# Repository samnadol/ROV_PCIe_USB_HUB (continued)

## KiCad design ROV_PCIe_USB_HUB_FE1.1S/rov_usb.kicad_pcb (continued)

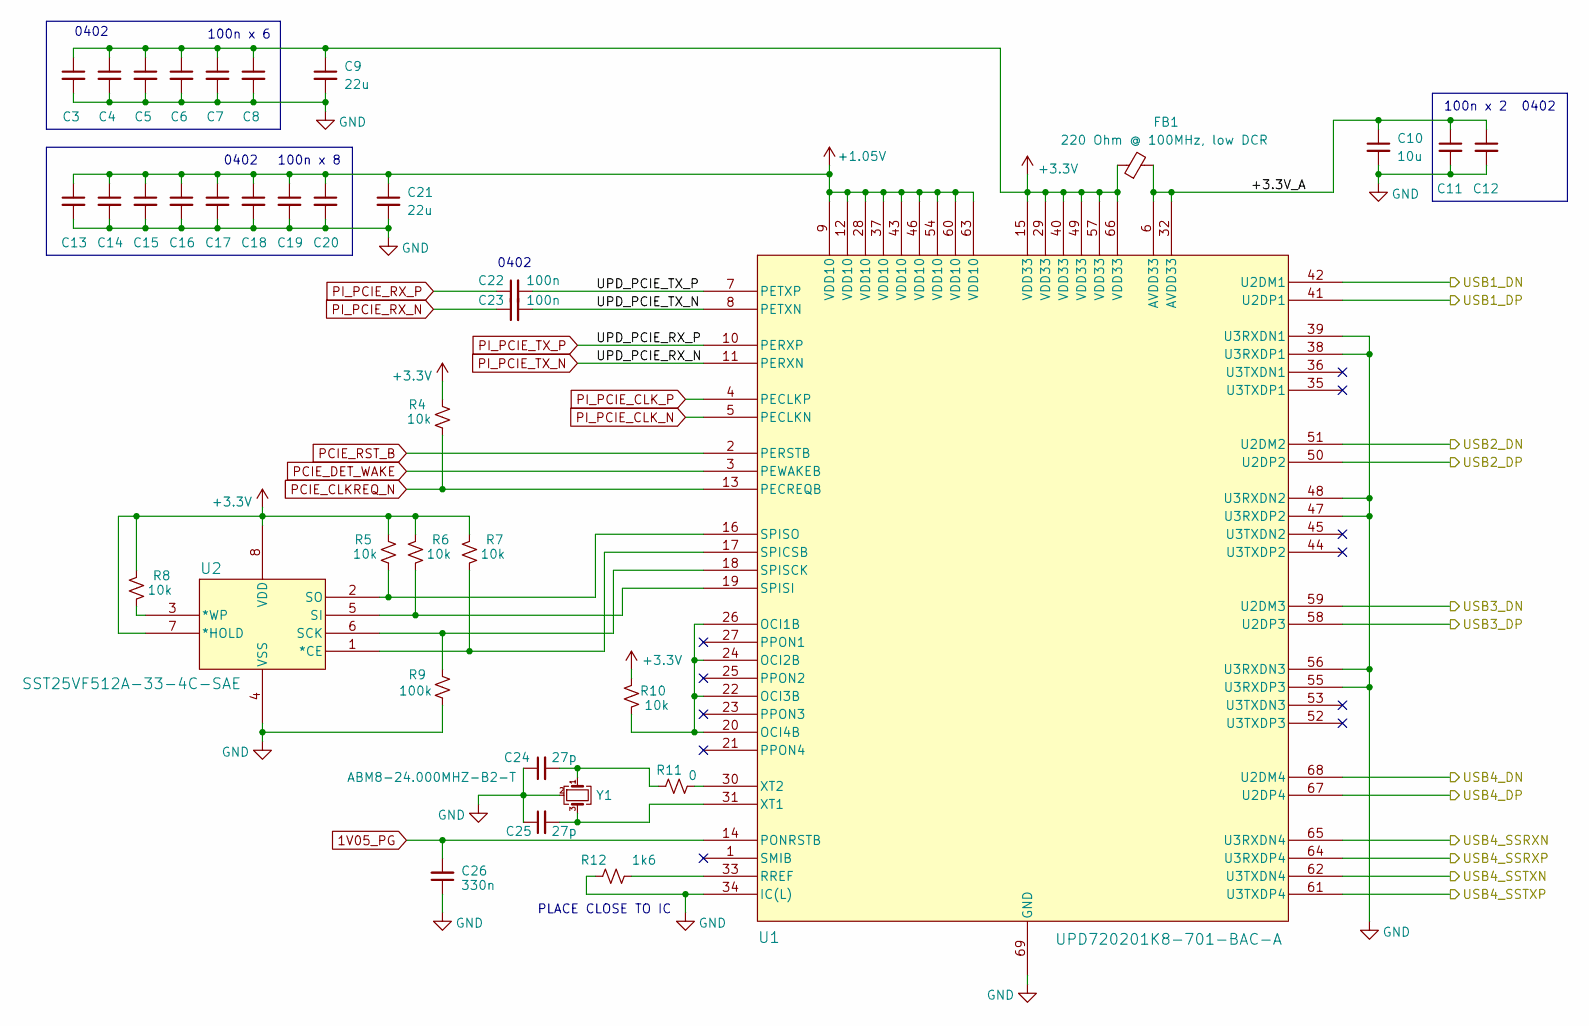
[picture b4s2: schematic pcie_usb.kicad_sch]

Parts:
C3, C4, C5, C6, C7, C8, C11, C12, C13, C14, C15, C16, C17, C18, C19, C20, C22, C23: 100n; C_0402_1005Metric; Part Number CL05B104KO5NNNC
C9, C21: 22u; C_0805_2012Metric; Part Number CL21A226MOQNNNE
C10: 10u; C_0805_2012Metric; Part Number CL21A106KOQNNNE
C24, C25: 27p; C_0402_1005Metric; Part Number CL05C270JB5NNNC
C26: 330n; C_0402_1005Metric; Part Number CL05A334KQ5NNNC
FB1: 220 Ohm @ 100MHz, low DCR; L_0805_2012Metric; Part Number BLM21PG221SN1D
R4, R5, R6, R7, R8, R10: 10k; R_0603_1608Metric; Part Number RC0603FR-0710KL
R9: 100k; R_0603_1608Metric; Part Number RC0603FR-07100KL
R11: 0; R_0402_1005Metric; Part Number RC0402JR-070RL
R12: 1k6; R_0603_1608Metric; Part Number RC0603FR-071K6L
U1: UPD720201K8-701-BAC-A; QFN68_8X8_REN; Part Number UPD720201K8-701-BAC-A
U2: SST25VF512A-33-4C-SAE; SST25VF512A; Part Number SST25VF512A-33-4C-SAE
Y1: ABM8-24.000MHZ-B2-T; Crystal_SMD_3225-4Pin_3.2x2.5mm; Part Number ABM8-24.000MHZ-B2-T

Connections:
1V05_PG: C26.2, U1.14 (PONRSTB); also elsewhere on the board
+1.05V: C13.1, C14.1, C15.1, C16.1, C17.1, C18.1, C19.1, C20.1, C21.1, U1.9 (VDD10), U1.12 (VDD10), U1.28 (VDD10), U1.37 (VDD10), U1.43 (VDD10), U1.46 (VDD10), U1.54 (VDD10), U1.60 (VDD10), U1.63 (VDD10); also elsewhere on the board
+3.3V: C3.1, C4.1, C5.1, C6.1, C7.1, C8.1, C9.1, FB1.1, R4.1, R5.1, R6.1, R7.1, R8.1, R10.1, U1.15 (VDD33), U1.29 (VDD33), U1.40 (VDD33), U1.49 (VDD33), U1.57 (VDD33), U1.66 (VDD33), U2.7 (*HOLD), U2.8 (VDD); also elsewhere on the board
/PCIe_USB/+3.3V_A: C10.1, C11.1, C12.1, FB1.2, U1.6 (AVDD33), U1.32 (AVDD33)
/PCIe_USB/UPD_PCIE_TX_N: C23.2, U1.8 (PETXN)
/PCIe_USB/UPD_PCIE_TX_P: C22.2, U1.7 (PETXP)
/PCIe_USB/USB1_DN: U1.42 (U2DM1); also elsewhere on the board
/PCIe_USB/USB1_DP: U1.41 (U2DP1); also elsewhere on the board
/PCIe_USB/USB2_DN: U1.51 (U2DM2); also elsewhere on the board
/PCIe_USB/USB2_DP: U1.50 (U2DP2); also elsewhere on the board
/PCIe_USB/USB3_DN: U1.59 (U2DM3); also elsewhere on the board
/PCIe_USB/USB3_DP: U1.58 (U2DP3); also elsewhere on the board
/PCIe_USB/USB4_DN: U1.68 (U2DM4); also elsewhere on the board
/PCIe_USB/USB4_DP: U1.67 (U2DP4); also elsewhere on the board
/PCIe_USB/USB4_SSRXN: U1.65 (U3RXDN4); also elsewhere on the board
/PCIe_USB/USB4_SSRXP: U1.64 (U3RXDP4); also elsewhere on the board
/PCIe_USB/USB4_SSTXN: U1.62 (U3TXDN4); also elsewhere on the board
/PCIe_USB/USB4_SSTXP: U1.61 (U3TXDP4); also elsewhere on the board
GND: C3.2, C4.2, C5.2, C6.2, C7.2, C8.2, C9.2, C10.2, C11.2, C12.2, C13.2, C14.2, C15.2, C16.2, C17.2, C18.2, C19.2, C20.2, C21.2, C24.1, C25.1, C26.1, R9.2, R12.1, U1.34 (IC(L)), U1.38 (U3RXDP1), U1.39 (U3RXDN1), U1.47 (U3RXDP2), U1.48 (U3RXDN2), U1.55 (U3RXDP3), U1.56 (U3RXDN3), U1.69 (GND), U2.4 (VSS), Y1.2 (G), Y1.4 (G); also elsewhere on the board
unnamed: C24.2, R11.1, Y1.1
unnamed: R10.2, U1.20 (OCI4B), U1.22 (OCI3B), U1.24 (OCI2B), U1.26 (OCI1B)
unnamed: R12.2, U1.33 (RREF)
unnamed: R7.2, U1.17 (SPICSB), U2.1 (*CE)
unnamed: R9.1, U1.18 (SPISCK), U2.6 (SCK)
unnamed: R6.2, U1.19 (SPISI), U2.5 (SI)
unnamed: R5.2, U1.16 (SPISO), U2.2 (SO)
unnamed: C25.2, U1.31 (XT1), Y1.3
unnamed: R11.2, U1.30 (XT2)
unnamed: R8.2, U2.3 (*WP)
PCIE_CLKREQ_N: R4.2, U1.13 (PECREQB); also elsewhere on the board
PCIE_DET_WAKE: U1.3 (PEWAKEB); also elsewhere on the board
PCIE_RST_B: U1.2 (PERSTB); also elsewhere on the board
PI_PCIE_CLK_N: U1.5 (PECLKN); also elsewhere on the board
PI_PCIE_CLK_P: U1.4 (PECLKP); also elsewhere on the board
PI_PCIE_RX_N: C23.1; also elsewhere on the board
PI_PCIE_RX_P: C22.1; also elsewhere on the board
PI_PCIE_TX_N: U1.11 (PERXN); also elsewhere on the board
PI_PCIE_TX_P: U1.10 (PERXP); also elsewhere on the board

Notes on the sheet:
0402
100n x 6
100n x 2
PLACE CLOSE TO IC
100n x 8

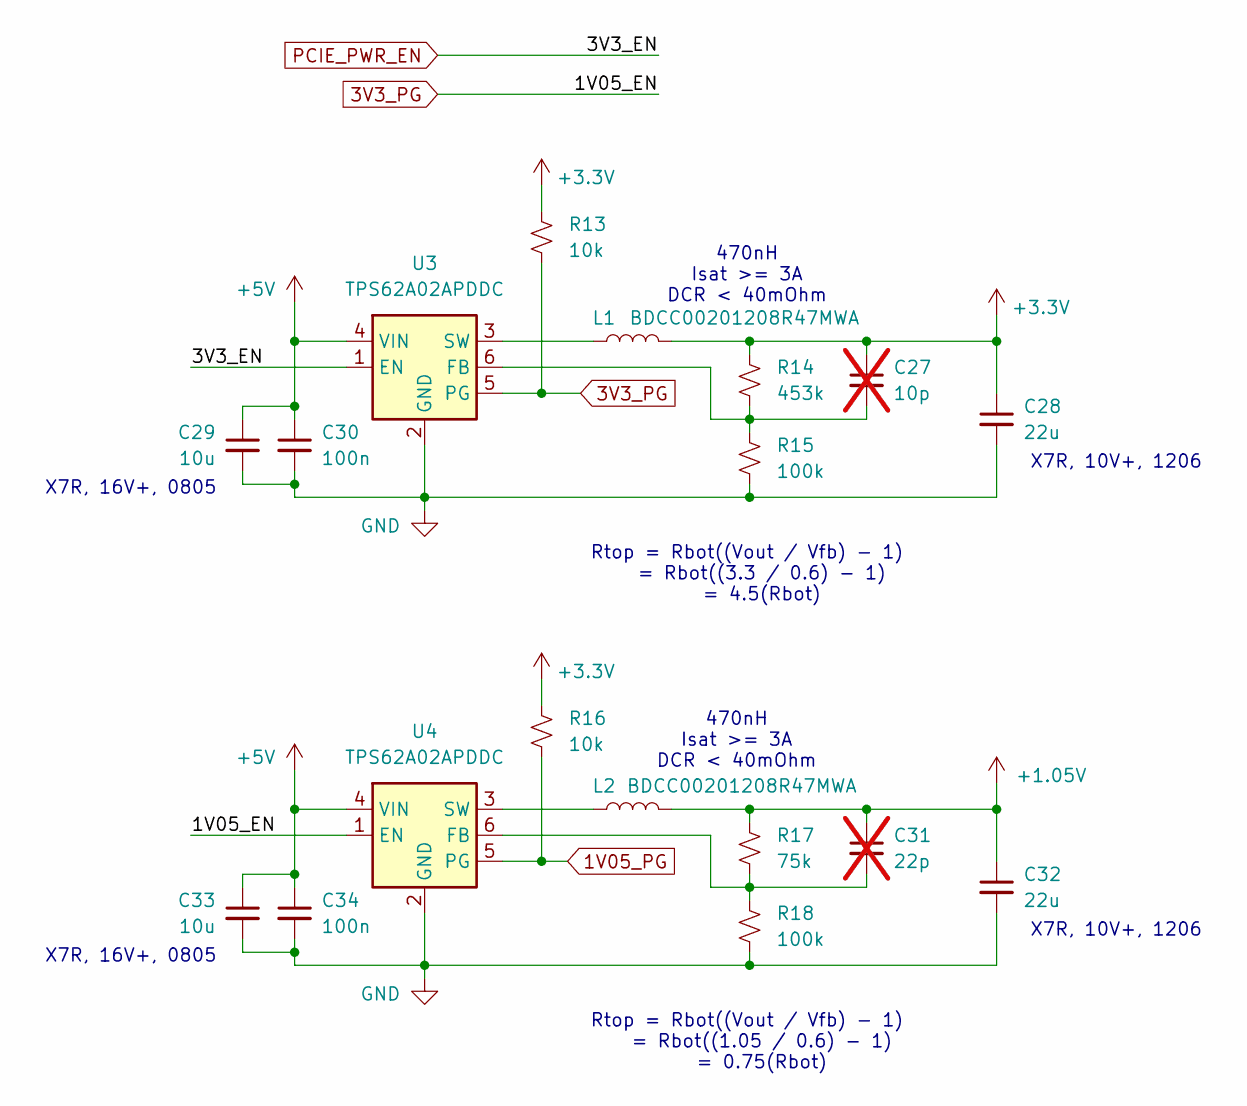
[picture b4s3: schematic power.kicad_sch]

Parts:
C27: 10p; C_0402_1005Metric; Part Number CL05C100JB5NNNC; not fitted
C28, C32: 22u; C_0805_2012Metric; Part Number CL21A226MOQNNNE
C29, C33: 10u; C_0805_2012Metric; Part Number CL21A106KOQNNNE
C30, C34: 100n; C_0402_1005Metric; Part Number CL05B104KO5NNNC
C31: 22p; C_0402_1005Metric; Part Number CL05C180JB5NNNC; not fitted
L1, L2: BDCC00201208R47MWA; L_0805_2012Metric; Part Number BDCC00201208R47MWA
R13, R16: 10k; R_0603_1608Metric; Part Number RC0603FR-0710KL
R14: 453k; R_0603_1608Metric; Part Number RC0603FR-07453KL
R15, R18: 100k; R_0603_1608Metric; Part Number RC0603FR-07100KL
R17: 75k; R_0603_1608Metric; Part Number RC0603FR-0775KL
U3, U4: TPS62A02APDDC; SOT-23-6; Part Number TPS62A02APDDC

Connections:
1V05_PG: R16.2, U4.5 (PG); also elsewhere on the board
3V3_PG: R13.2, U3.5 (PG), U4.1 (EN)
+1.05V: C31.1, C32.1, L2.2, R17.1; also elsewhere on the board
+3.3V: C27.1, C28.1, L1.2, R13.1, R14.1, R16.1; also elsewhere on the board
+5V: C29.1, C30.1, C33.1, C34.1, U3.4 (VIN), U4.4 (VIN); also elsewhere on the board
GND: C28.2, C29.2, C30.2, C32.2, C33.2, C34.2, R15.2, R18.2, U3.2 (GND), U4.2 (GND); also elsewhere on the board
unnamed: C27.2, R14.2, R15.1, U3.6 (FB)
unnamed: L1.1, U3.3 (SW)
unnamed: C31.2, R17.2, R18.1, U4.6 (FB)
unnamed: L2.1, U4.3 (SW)
PCIE_PWR_EN: U3.1 (EN); also elsewhere on the board

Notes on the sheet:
X7R, 10V+, 1206
470nH Isat >= 3A DCR < 40mOhm
X7R, 16V+, 0805
Rtop = Rbot((Vout / Vfb) - 1) = Rbot((3.3 / 0.6) - 1) = 4.5(Rbot)
Rtop = Rbot((Vout / Vfb) - 1) = Rbot((1.05 / 0.6) - 1) = 0.75(Rbot)

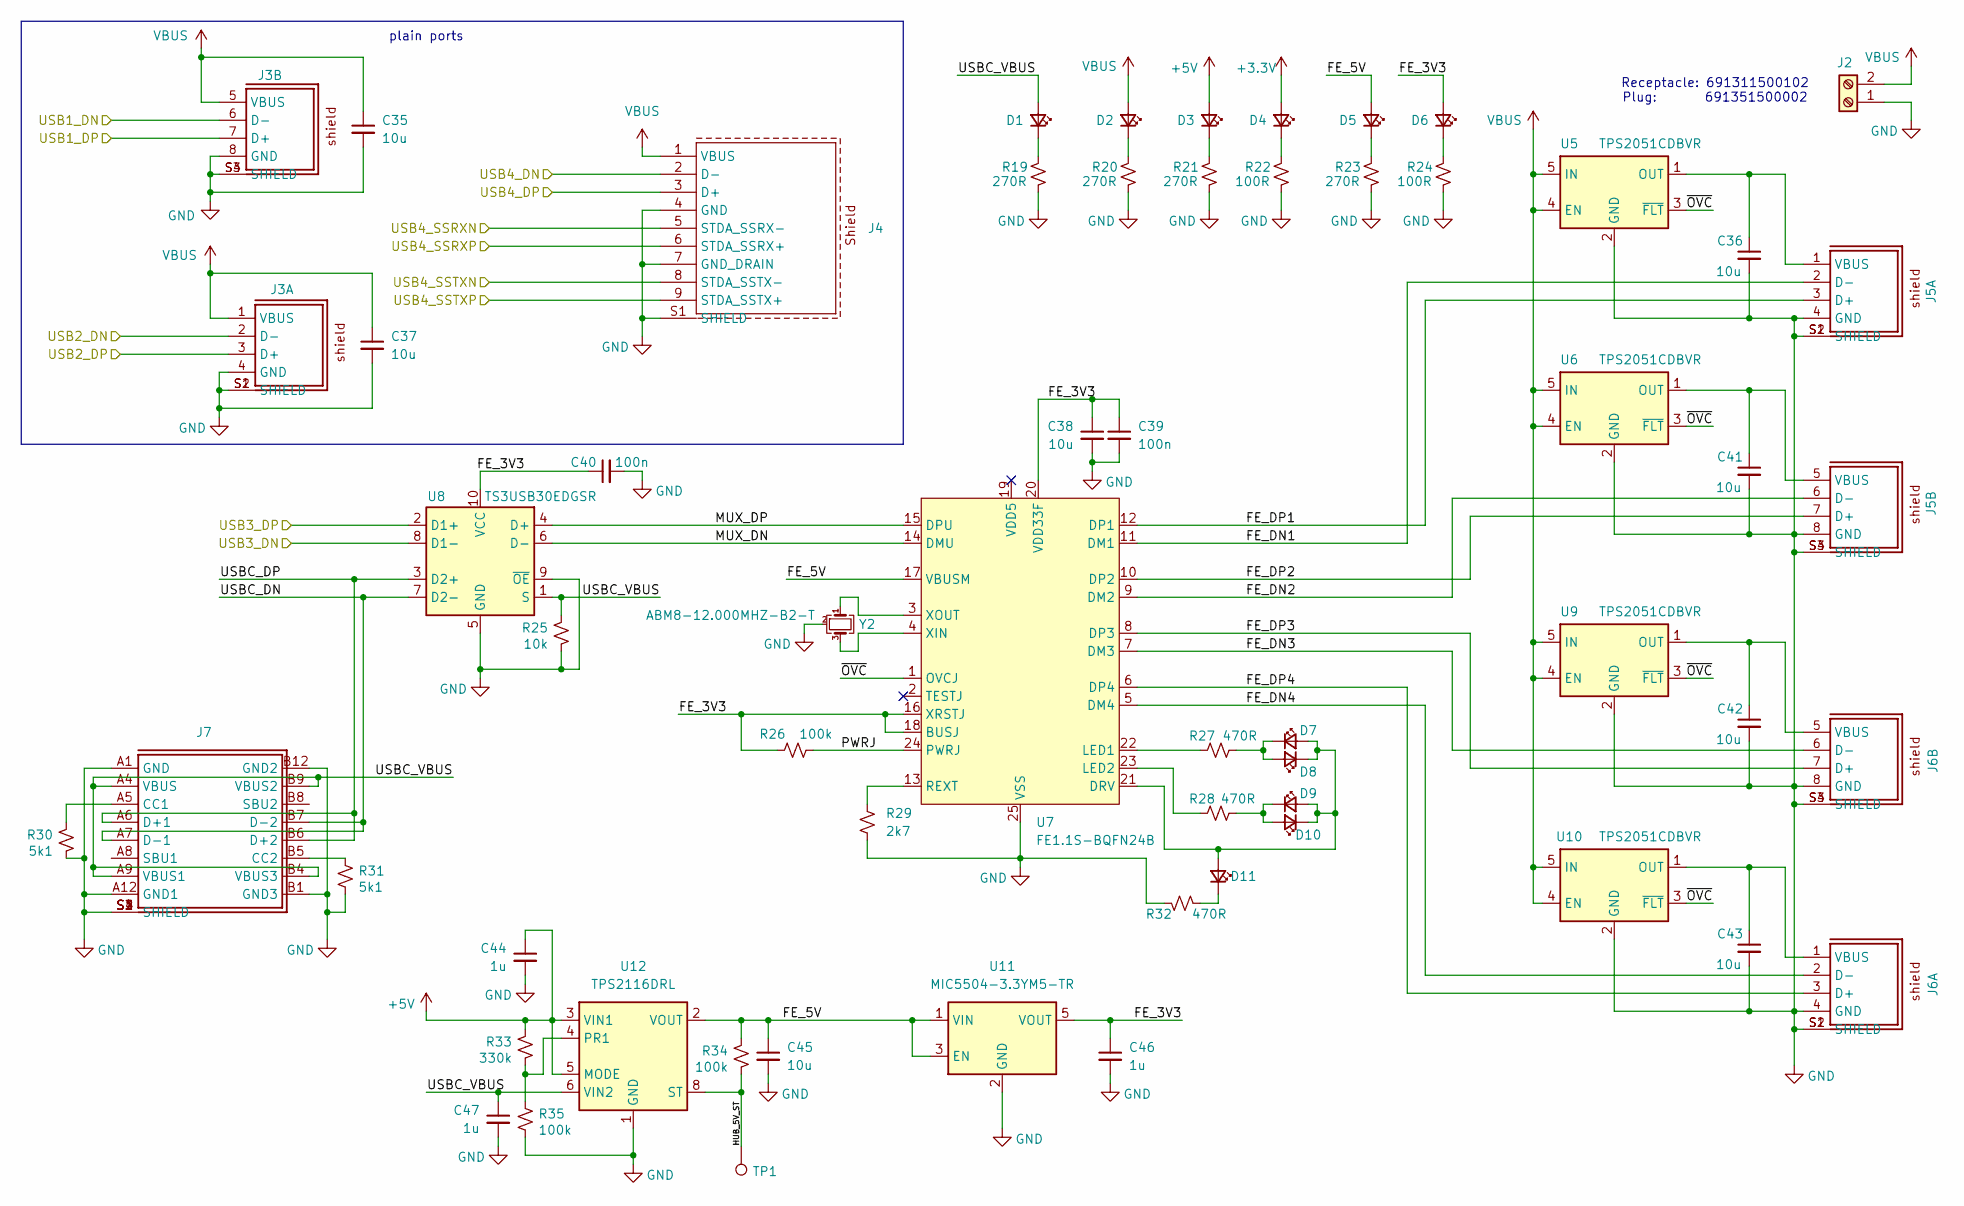
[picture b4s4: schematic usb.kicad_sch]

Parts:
C35, C36, C37, C38, C41, C42, C43, C45: 10u; C_0805_2012Metric; Part Number CL21A106KOQNNNE
C39, C40: 100n; C_0402_1005Metric; Part Number CL05B104KO5NNNC
C44, C46, C47: 1u; C_0603_1608Metric; Part Number CL10B105KO8NNNC
D1, D2, D3, D4, D5, D6, D7, D8, D9, D10: Green; LED_0603_1608Metric; Part Number LTST-C190KGKT
D11: Red; LED_0603_1608Metric; Part Number LTST-C191KRKT
J2: 691311500102; J_Wurth_WR-TBL_691311500102; Part Number 691311500102
J3, J5, J6: USB-A-D-RA; J_Wurth_WR-USB_61400826021; Working Voltage (V (AC)) 30; Part Number USB-A-D-RA
J4: USB-A3-S-VT-CS5A; J_Wurth_WR-USB_692121430000; Working Voltage(V (AC)) 30 V (AC); Part Number USB-A3-S-VT-CS5A
J7: 629722000214; J_Wurth_WR-USB_629722000214; Working Voltage (V (AC)) 20; Part Number 629722000214
R19, R20, R21, R23: 270R; R_0603_1608Metric; Part Number RC0603FR-07270RL
R22, R24: 100R; R_0603_1608Metric; Part Number RC0603FR-07100RL
R25: 10k; R_0603_1608Metric; Part Number RC0603FR-0710KL
R26, R34, R35: 100k; R_0603_1608Metric; Part Number RC0603FR-07100KL
R27, R28, R32: 470R; R_0603_1608Metric; Part Number RC0603FR-07470RL
R29: 2k7; R_0603_1608Metric; Part Number RC0603FR-072K7L
R30, R31: 5k1; R_0603_1608Metric; Part Number RC0603FR-075K1L
R33: 330k; R_0603_1608Metric; Part Number RC0603FR-07330KL
TP1: TestPoint; TestPoint_Pad_1.0x1.0mm
U5, U6, U9, U10: TPS2051CDBVR; SOT-23-5; Part Number TPS2051CDBVR
U7: FE1.1S-BQFN24B; WQFN-24-1EP_4x4mm_P0.5mm_EP2.45x2.45mm; Part Number FE1.1S-BQFN24B
U8: TS3USB30EDGSR; TSSOP-10_3x3mm_P0.5mm; Part Number TS3USB30EDGSR
U11: MIC5504-3.3YM5-TR; SOT-23-5; Part Number MIC5504-3.3YM5-TR
U12: TPS2116DRL; SOT-583-8; Part Number TPS2116DRL
Y2: ABM8-12.000MHZ-B2-T; Crystal_SMD_3225-4Pin_3.2x2.5mm; Part Number ABM8-12.000MHZ-B2-T

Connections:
+3.3V: D4.2 (A); also elsewhere on the board
+5V: C44.1, D3.2 (A), R33.2, U12.3 (VIN1), U12.5 (MODE); also elsewhere on the board
/PCIe_USB/USB1_DN: J3.6 (D-); also elsewhere on the board
/PCIe_USB/USB1_DP: J3.7 (D+); also elsewhere on the board
/PCIe_USB/USB2_DN: J3.2 (D-); also elsewhere on the board
/PCIe_USB/USB2_DP: J3.3 (D+); also elsewhere on the board
/PCIe_USB/USB3_DN: U8.8 (D1-); also elsewhere on the board
/PCIe_USB/USB3_DP: U8.2 (D1+); also elsewhere on the board
/PCIe_USB/USB4_DN: J4.2 (D-); also elsewhere on the board
/PCIe_USB/USB4_DP: J4.3 (D+); also elsewhere on the board
/PCIe_USB/USB4_SSRXN: J4.5 (STDA_SSRX-); also elsewhere on the board
/PCIe_USB/USB4_SSRXP: J4.6 (STDA_SSRX+); also elsewhere on the board
/USB/FE_3V3: C38.1, C39.1, C40.1, C46.1, D6.2 (A), R26.2, U7.16 (XRSTJ), U7.18 (BUSJ), U7.20 (VDD33F), U8.10 (VCC), U11.5 (VOUT)
/USB/FE_5V: C45.1, D5.2 (A), R34.2, U7.17 (VBUSM), U11.1 (VIN), U11.3 (EN), U12.2 (VOUT), U12.7 (VOUT)
/USB/FE_DN1: J5.2 (D-), U7.11 (DM1)
/USB/FE_DN2: J5.6 (D-), U7.9 (DM2)
/USB/FE_DN3: J6.6 (D-), U7.7 (DM3)
/USB/FE_DN4: J6.2 (D-), U7.5 (DM4)
/USB/FE_DP1: J5.3 (D+), U7.12 (DP1)
/USB/FE_DP2: J5.7 (D+), U7.10 (DP2)
/USB/FE_DP3: J6.7 (D+), U7.8 (DP3)
/USB/FE_DP4: J6.3 (D+), U7.6 (DP4)
/USB/HUB_5V_ST: R34.1, TP1.1 (1_1), U12.8 (ST)
/USB/MUX_DN: U7.14 (DMU), U8.6 (D-)
/USB/MUX_DP: U7.15 (DPU), U8.4 (D+)
/USB/PWRJ: R26.1, U7.24 (PWRJ)
/USB/USB4_SSTXN: J4.8 (STDA_SSTX-); also elsewhere on the board
/USB/USB4_SSTXP: J4.9 (STDA_SSTX+); also elsewhere on the board
/USB/USBC_DN: J7.A7 (D-1), J7.B7 (D-2), U8.7 (D2-)
/USB/USBC_DP: J7.A6 (D+1), J7.B6 (D+2), U8.3 (D2+)
/USB/USBC_VBUS: C47.1, D1.2 (A), J7.A4 (VBUS), J7.A9 (VBUS1), J7.B4 (VBUS3), J7.B9 (VBUS2), R25.2, U8.1 (S), U12.6 (VIN2)
/USB/~OVC: U5.3 (~FLT), U6.3 (~FLT), U7.1 (OVCJ), U9.3 (~FLT), U10.3 (~FLT)
GND: C35.2, C36.2, C37.2, C38.2, C39.2, C40.2, C41.2, C42.2, C43.2, C44.2, C45.2, C46.2, C47.2, J2.1, J3.4 (GND), J3.8 (GND), J3.S1 (SHIELD), J3.S2 (SHIELD), J3.S3 (SHIELD), J3.S4 (SHIELD), J4.4 (GND), J4.7 (GND_DRAIN), J4.S1 (SHIELD), J4.S2 (SHIELD), J5.4 (GND), J5.8 (GND), J5.S1 (SHIELD), J5.S2 (SHIELD), J5.S3 (SHIELD), J5.S4 (SHIELD), J6.4 (GND), J6.8 (GND), J6.S1 (SHIELD), J6.S2 (SHIELD), J6.S3 (SHIELD), J6.S4 (SHIELD), J7.A1 (GND), J7.A12 (GND1), J7.B1 (GND3), J7.B12 (GND2), J7.S1 (SHIELD), J7.S2 (SHIELD), J7.S3 (SHIELD), J7.S4 (SHIELD), R19.1, R20.1, R21.1, R22.1, R23.1, R24.1, R25.1, R29.2, R30.1, R31.1, R32.1, R35.1, U5.2 (GND), U6.2 (GND), U7.25 (VSS), U8.5 (GND), U8.9 (~OE), U9.2 (GND), U10.2 (GND), U11.2 (GND), U12.1 (GND), Y2.2 (G), Y2.4 (G); also elsewhere on the board
unnamed: D1.1 (K), R19.2
unnamed: D2.1 (K), R20.2
unnamed: D3.1 (K), R21.2
unnamed: D4.1 (K), R22.2
unnamed: D5.1 (K), R23.2
unnamed: D6.1 (K), R24.2
unnamed: D7.1 (K), D8.2 (A), R27.2
unnamed: D9.1 (K), D10.2 (A), R28.2
unnamed: D7.2 (A), D8.1 (K), D9.2 (A), D10.1 (K), D11.2 (A), U7.21 (DRV)
unnamed: D11.1 (K), R32.2
unnamed: C36.1, J5.1 (VBUS), U5.1 (OUT)
unnamed: C41.1, J5.5 (VBUS), U6.1 (OUT)
unnamed: C43.1, J6.1 (VBUS), U10.1 (OUT)
unnamed: C42.1, J6.5 (VBUS), U9.1 (OUT)
unnamed: J7.A5 (CC1), R30.2
unnamed: J7.B5 (CC2), R31.2
unnamed: R27.1, U7.22 (LED1)
unnamed: R28.1, U7.23 (LED2)
unnamed: R29.1, U7.13 (REXT)
unnamed: U7.4 (XIN), Y2.3
unnamed: U7.3 (XOUT), Y2.1
unnamed: R33.1, R35.2, U12.4 (PR1)
VBUS: C35.1, C37.1, D2.2 (A), J2.2, J3.1 (VBUS), J3.5 (VBUS), J4.1 (VBUS), U5.4 (EN), U5.5 (IN), U6.4 (EN), U6.5 (IN), U9.4 (EN), U9.5 (IN), U10.4 (EN), U10.5 (IN)

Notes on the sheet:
Receptacle: 691311500102 Plug: 691351500002
plain ports

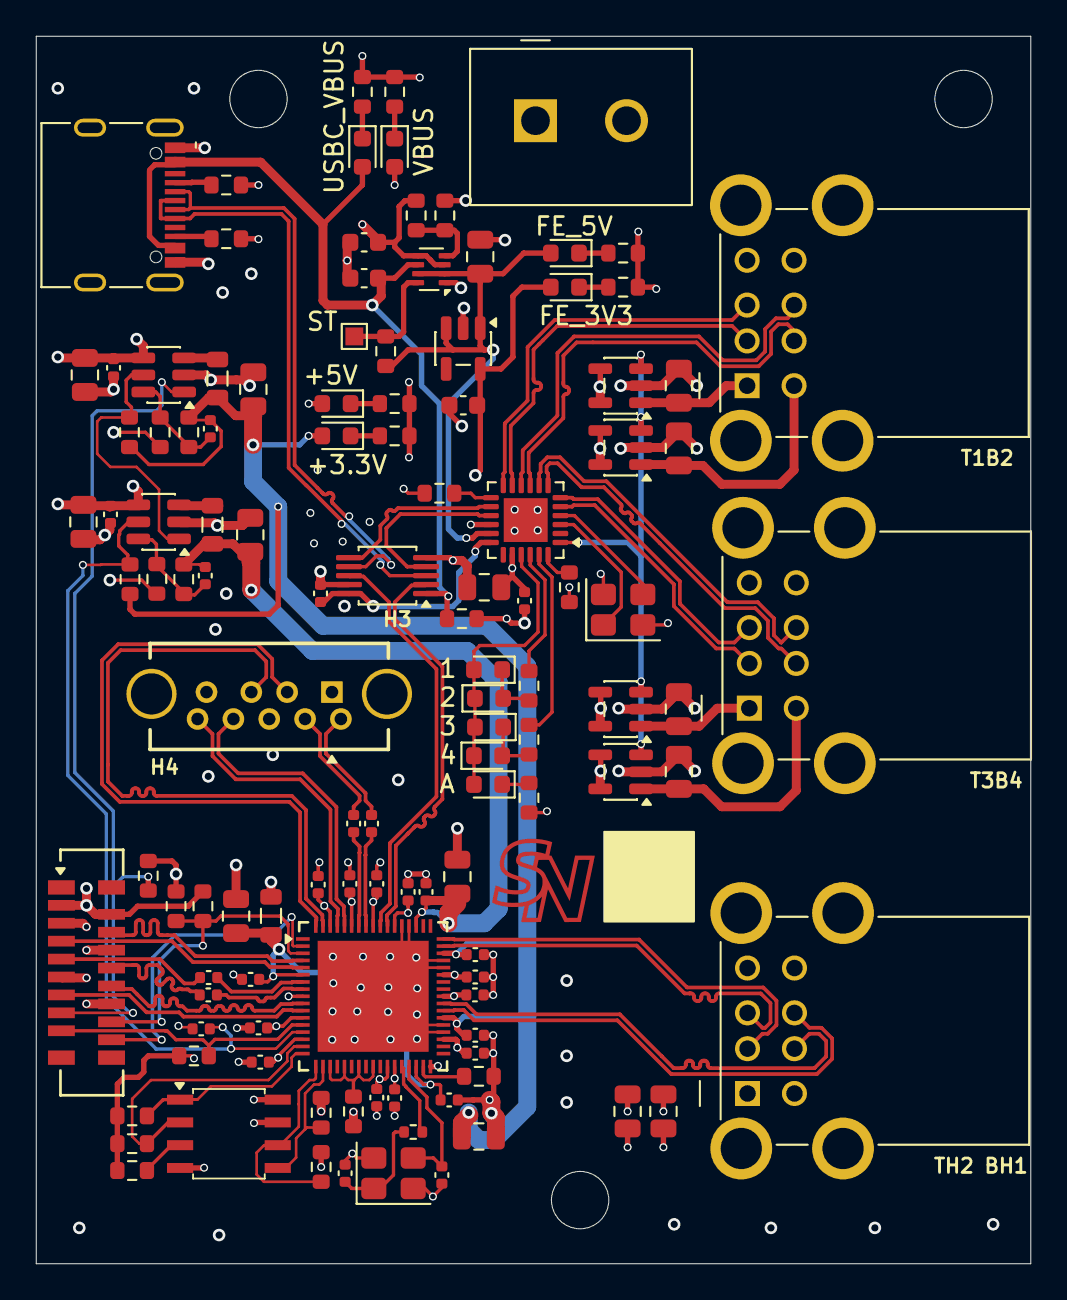
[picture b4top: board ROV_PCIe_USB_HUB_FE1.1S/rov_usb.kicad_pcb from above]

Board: 4 copper layers, 55.5 x 68.5 mm, 121 parts (0 on the bottom side), 88 nets.

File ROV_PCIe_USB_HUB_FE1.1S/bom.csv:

"Reference","Value","Part Number","Footprint","Qty","DNP"
"R11","0","RC0402JR-070RL","Resistor_SMD:R_0402_1005Metric","1",""
"C24,C25","27p","CL05C270JB5NNNC ","Capacitor_SMD:C_0402_1005Metric","2",""
"C1,C2,C3,C4,C5,C6,C7,C8,C11,C12,C13,C14,C15,C16,C17,C18,C19,C20,C22,C23,C30,C34,C39,C40","100n","CL05B104KO5NNNC","Capacitor_SMD:C_0402_1005Metric","24",""
"C26","330n","CL05A334KQ5NNNC","Capacitor_SMD:C_0402_1005Metric","1",""
"C44,C46,C47","1u","CL10B105KO8NNNC","Capacitor_SMD:C_0603_1608Metric","3",""
"C10,C29,C33,C35,C36,C37,C38,C41,C42,C43,C45","10u","CL21A106KOQNNNE ","Capacitor_SMD:C_0805_2012Metric","11",""
"C9,C21,C28,C32","22u","CL21A226MOQNNNE","Capacitor_SMD:C_0805_2012Metric","4",""
"R35,R36","100R","RC0603FR-07100RL","Resistor_SMD:R_0603_1608Metric","2",""
"R31,R32,R33,R34","270R","RC0603FR-07270RL","Resistor_SMD:R_0603_1608Metric","4",""
"R21,R22,R26","470R","RC0603FR-07470RL","Resistor_SMD:R_0603_1608Metric","3",""
"R12","1k6","RC0603FR-071K6L","Resistor_SMD:R_0603_1608Metric","1",""
"R23","2k7","RC0603FR-072K7L","Resistor_SMD:R_0603_1608Metric","1",""
"R1","3k6","RC0603FR-073K6L","Resistor_SMD:R_0603_1608Metric","1",""
"R24,R25","5k1","RC0603FR-075K1L","Resistor_SMD:R_0603_1608Metric","2",""
"R3","6k8","RC0603FR-076K8L","Resistor_SMD:R_0603_1608Metric","1",""
"R4,R5,R6,R7,R8,R10,R13,R16,R19","10k","RC0603FR-0710KL","Resistor_SMD:R_0603_1608Metric","9",""
"R17","75k","RC0603FR-0775KL","Resistor_SMD:R_0603_1608Metric","1",""
"R2,R9,R15,R18,R20,R28,R29","100k","RC0603FR-07100KL","Resistor_SMD:R_0603_1608Metric","7",""
"R27","330k","RC0603FR-07330KL","Resistor_SMD:R_0603_1608Metric","1",""
"R14","453k","RC0603FR-07453KL","Resistor_SMD:R_0603_1608Metric","1",""
"J1","525591652","525591652","snadol:525591652","1",""
"J7","629722000214","629722000214","Connector_SMD_Wurth:J_Wurth_WR-USB_629722000214","1",""
"J3","691311500102","691311500102","Connector_THT_Wurth:J_Wurth_WR-TBL_691311500102","1",""
"FB1","220 Ohm @ 100MHz, low DCR","BLM21PG221SN1D","Inductor_SMD:L_0805_2012Metric","1",""
"Y2","ABM8-12.000MHZ-B2-T","ABM8-12.000MHZ-B2-T","Crystal:Crystal_SMD_3225-4Pin_3.2x2.5mm","1",""
"Y1","ABM8-24.000MHZ-B2-T","ABM8-24.000MHZ-B2-T","Crystal:Crystal_SMD_3225-4Pin_3.2x2.5mm","1",""
"L1,L2","BDCC00201208R47MWA","BDCC00201208R47MWA","Inductor_SMD:L_0805_2012Metric","2",""
"U7","FE1.1S-BQFN24B","FE1.1S-BQFN24B","Package_DFN_QFN:WQFN-24-1EP_4x4mm_P0.5mm_EP2.45x2.45mm","1",""
"D1,D2,D3,D4,D7,D8,D9,D10,D11,D12","Green","LTST-C190KGKT","LED_SMD:LED_0603_1608Metric","10",""
"U11","MIC5504-3.3YM5-TR","MIC5504-3.3YM5-TR","Package_TO_SOT_SMD:SOT-23-5","1",""
"D5","Red","LTST-C191KRKT","LED_SMD:LED_0603_1608Metric","1",""
"U2","SST25VF512A-33-4C-SAE","SST25VF512A-33-4C-SAE","snadol:SST25VF512A","1",""
"U5,U6,U9,U10","TPS2051CDBVR","TPS2051CDBVR","Package_TO_SOT_SMD:SOT-23-5","4",""
"U12","TPS2116DRL","TPS2116DRL","Package_TO_SOT_SMD:SOT-583-8","1",""
"U3,U4","TPS62A02APDDC","TPS62A02APDDC","Package_TO_SOT_SMD:SOT-23-6","2",""
"U8","TS3USB30EDGSR","TS3USB30EDGSR","Package_SO:TSSOP-10_3x3mm_P0.5mm","1",""
"U1","UPD720201K8-701-BAC-A","UPD720201K8-701-BAC-A","snadol:QFN68_8X8_REN","1",""
"J2,J5,J6","USB-A-D-RA","USB-A-D-RA","Connector_THT_Wurth:J_Wurth_WR-USB_61400826021","3",""
"J4","USB-A3-S-VT-CS5A","USB-A3-S-VT-CS5A","Connector_THT_Wurth:J_Wurth_WR-USB_692121430000","1",""
